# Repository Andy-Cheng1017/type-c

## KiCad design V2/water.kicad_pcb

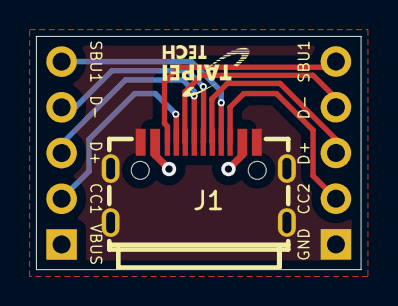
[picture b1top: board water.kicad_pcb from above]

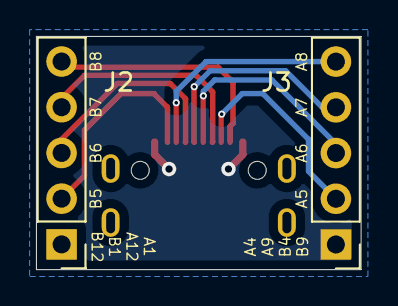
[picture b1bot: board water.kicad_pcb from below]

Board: 2 copper layers, 18.0 x 13.0 mm, 3 parts (2 on the bottom side), 10 nets.

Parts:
J1: USB_C_Receptacle_USB2.0; USB-C-SMD_TYPE-C-31-E-03
J2, J3: Conn_01x05; PinHeader_1x05_P2.54mm_Vertical

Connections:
unnamed: J1.A1 (GND), J1.A12 (GND), J1.B1 (GND), J1.B12 (GND), J1.S1 (SHIELD), J2.1
unnamed: J1.A4 (VBUS), J1.A9 (VBUS), J1.B4 (VBUS), J1.B9 (VBUS), J3.1
unnamed: J1.A5 (CC1), J3.2
unnamed: J1.A6 (D+), J3.3
unnamed: J1.A7 (D-), J3.4
unnamed: J1.A8 (SBU1), J3.5
unnamed: J1.B5 (CC2), J2.2
unnamed: J1.B6 (D+), J2.3
unnamed: J1.B7 (D-), J2.4
unnamed: J1.B8 (SBU2), J2.5

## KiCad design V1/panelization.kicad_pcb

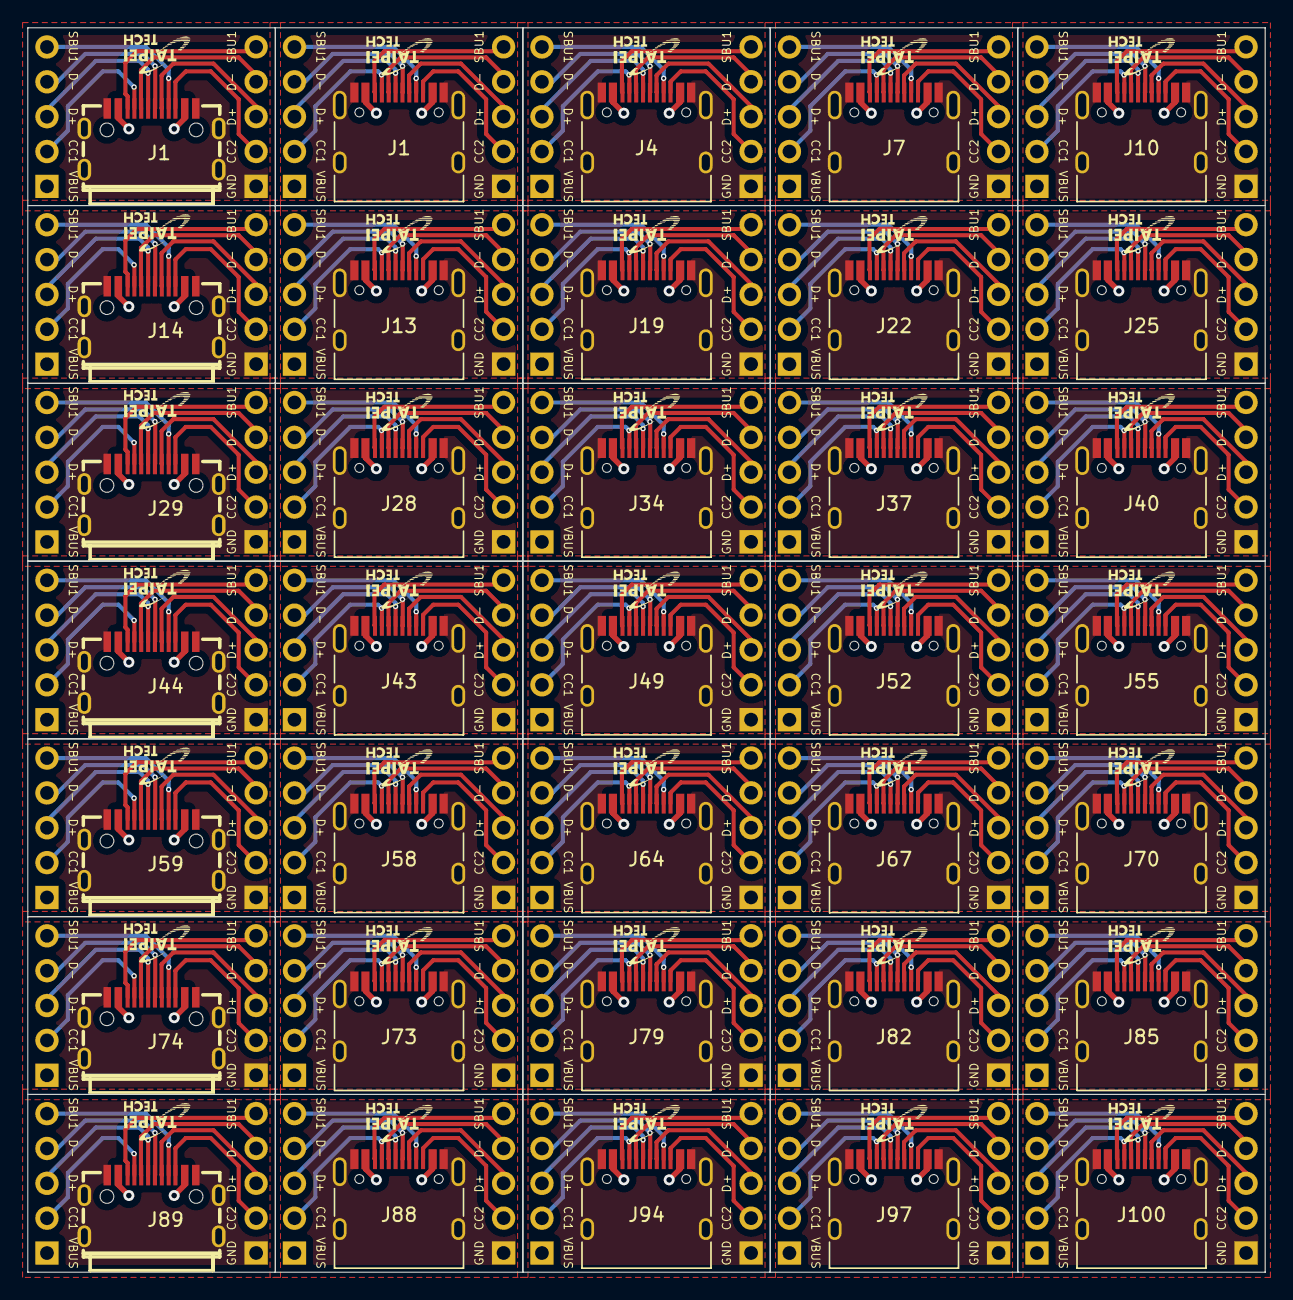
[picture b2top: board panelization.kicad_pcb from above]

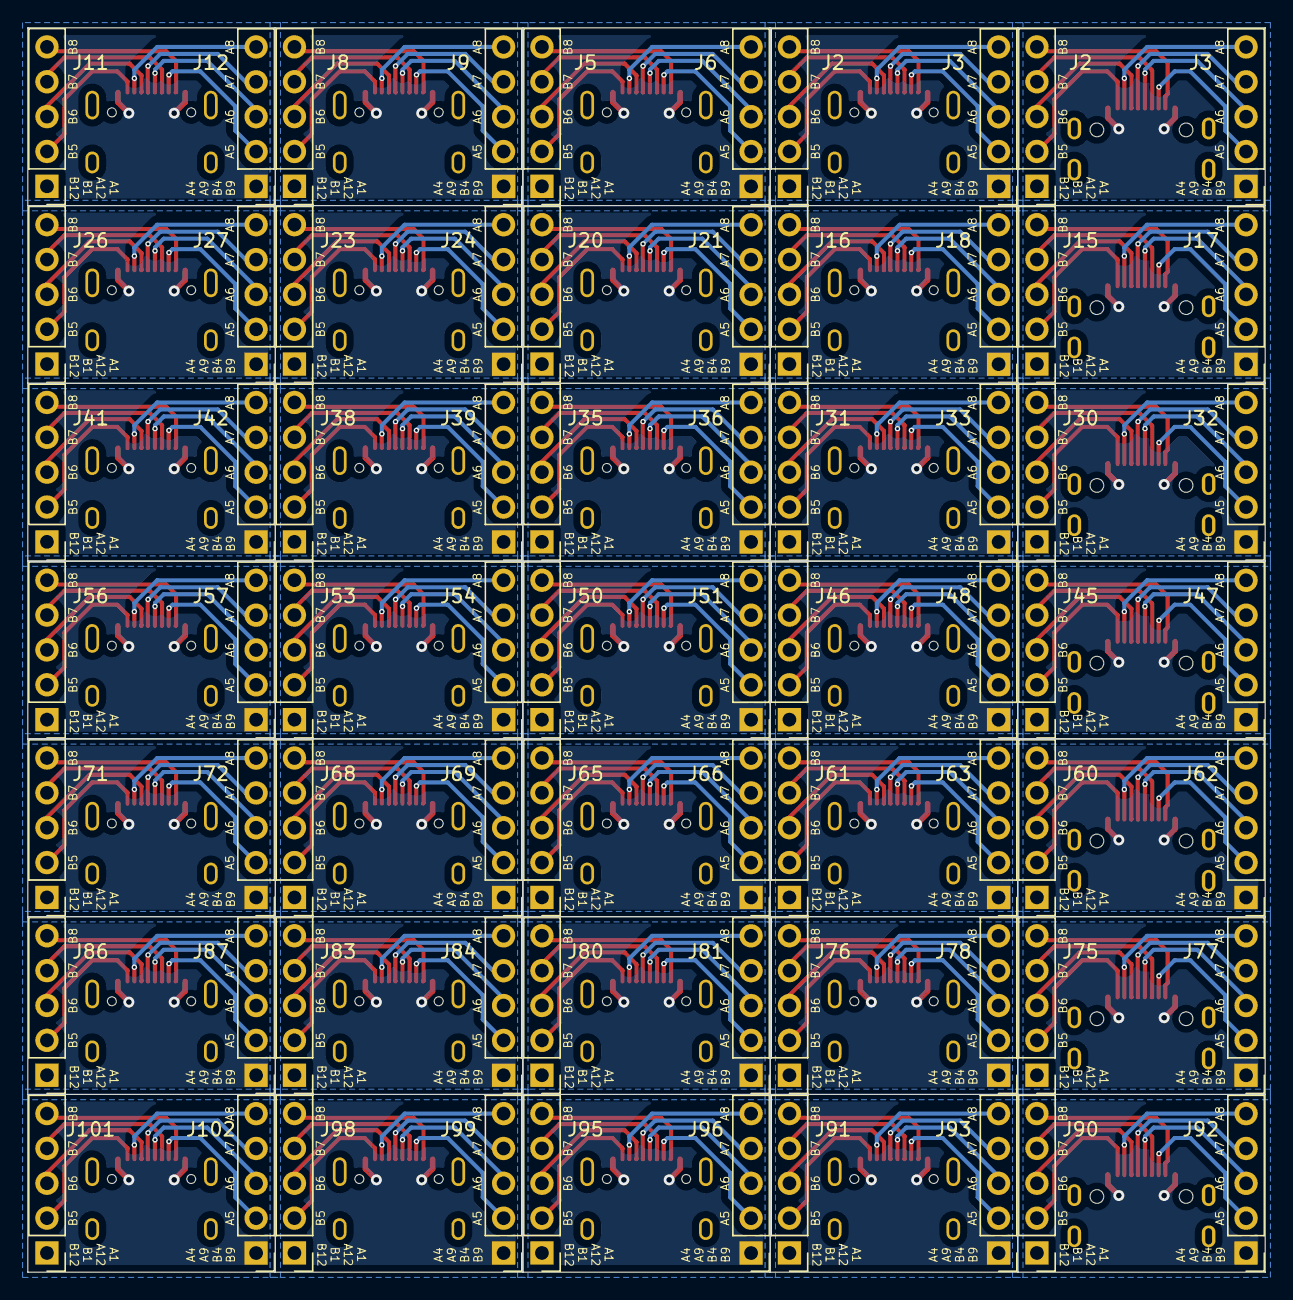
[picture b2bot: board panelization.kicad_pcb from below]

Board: 2 copper layers, 90.2 x 90.7 mm, 105 parts (70 on the bottom side), 10 nets.

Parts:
J1, J4, J7, J10, J13, J19, J22, J25, J28, J34, J37, J40, J43, J49, J52, J55, J58, J64, J67, J70, J73, J79, J82, J85, J88, J94, J97, J100: USB_C_Receptacle_USB2.0; USB_C_Receptacle_HRO_TYPE-C-31-M-12
J1#2, J14, J29, J44, J59, J74, J89: USB_C_Receptacle_USB2.0; USB-C-SMD_TYPE-C-31-E-03
J2, J2#2, J3, J3#2, J5, J6, J8, J9, J11, J12, J15, J16, J17, J18, J20, J21, J23, J24, J26, J27, J30, J31, J32, J33, J35, J36, J38, J39, J41, J42, J45, J46, J47, J48, J50, J51, J53, J54, J56, J57, J60, J61, J62, J63, J65, J66, J68, J69, J71, J72, J75, J76, J77, J78, J80, J81, J83, J84, J86, J87, J90, J91, J92, J93, J95, J96, J98, J99, J101, J102: Conn_01x05; PinHeader_1x05_P2.54mm_Vertical

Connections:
unnamed: J1.A1 (GND), J1.A12 (GND), J1.B1 (GND), J1.B12 (GND), J1.S1 (SHIELD), J1#2.A1 (GND), J1#2.A12 (GND), J1#2.B1 (GND), J1#2.B12 (GND), J1#2.S1 (SHIELD), J2.1, J2#2.1, J4.A1 (GND), J4.A12 (GND), J4.B1 (GND), J4.B12 (GND), J4.S1 (SHIELD), J5.1, J7.A1 (GND), J7.A12 (GND), J7.B1 (GND), J7.B12 (GND), J7.S1 (SHIELD), J8.1, J10.A1 (GND), J10.A12 (GND), J10.B1 (GND), J10.B12 (GND), J10.S1 (SHIELD), J11.1, J13.A1 (GND), J13.A12 (GND), J13.B1 (GND), J13.B12 (GND), J13.S1 (SHIELD), J14.A1 (GND), J14.A12 (GND), J14.B1 (GND), J14.B12 (GND), J14.S1 (SHIELD), J15.1, J16.1, J19.A1 (GND), J19.A12 (GND), J19.B1 (GND), J19.B12 (GND), J19.S1 (SHIELD), J20.1, J22.A1 (GND), J22.A12 (GND), J22.B1 (GND), J22.B12 (GND), J22.S1 (SHIELD), J23.1, J25.A1 (GND), J25.A12 (GND), J25.B1 (GND), J25.B12 (GND), J25.S1 (SHIELD), J26.1, J28.A1 (GND), J28.A12 (GND), J28.B1 (GND), J28.B12 (GND), J28.S1 (SHIELD), J29.A1 (GND), J29.A12 (GND), J29.B1 (GND), J29.B12 (GND), J29.S1 (SHIELD), J30.1, J31.1, J34.A1 (GND), J34.A12 (GND), J34.B1 (GND), J34.B12 (GND), J34.S1 (SHIELD), J35.1, J37.A1 (GND), J37.A12 (GND), J37.B1 (GND), J37.B12 (GND), J37.S1 (SHIELD), J38.1, J40.A1 (GND), J40.A12 (GND), J40.B1 (GND), J40.B12 (GND), J40.S1 (SHIELD), J41.1, J43.A1 (GND), J43.A12 (GND), J43.B1 (GND), J43.B12 (GND), J43.S1 (SHIELD), J44.A1 (GND), J44.A12 (GND), J44.B1 (GND), J44.B12 (GND), J44.S1 (SHIELD), J45.1, J46.1, J49.A1 (GND), J49.A12 (GND), J49.B1 (GND), J49.B12 (GND), J49.S1 (SHIELD), J50.1, J52.A1 (GND), J52.A12 (GND), J52.B1 (GND), J52.B12 (GND), J52.S1 (SHIELD), J53.1, J55.A1 (GND), J55.A12 (GND), J55.B1 (GND), J55.B12 (GND), J55.S1 (SHIELD), J56.1, J58.A1 (GND), J58.A12 (GND), J58.B1 (GND), J58.B12 (GND), J58.S1 (SHIELD), J59.A1 (GND), J59.A12 (GND), J59.B1 (GND), J59.B12 (GND), J59.S1 (SHIELD), J60.1, J61.1, J64.A1 (GND), J64.A12 (GND), J64.B1 (GND), J64.B12 (GND), J64.S1 (SHIELD), J65.1, J67.A1 (GND), J67.A12 (GND), J67.B1 (GND), J67.B12 (GND), J67.S1 (SHIELD), J68.1, J70.A1 (GND), J70.A12 (GND), J70.B1 (GND), J70.B12 (GND), J70.S1 (SHIELD), J71.1, J73.A1 (GND), J73.A12 (GND), J73.B1 (GND), J73.B12 (GND), J73.S1 (SHIELD), J74.A1 (GND), J74.A12 (GND), J74.B1 (GND), J74.B12 (GND), J74.S1 (SHIELD), J75.1, J76.1, J79.A1 (GND), J79.A12 (GND), J79.B1 (GND), J79.B12 (GND), J79.S1 (SHIELD), J80.1, J82.A1 (GND), J82.A12 (GND), J82.B1 (GND), J82.B12 (GND), J82.S1 (SHIELD), J83.1, J85.A1 (GND), J85.A12 (GND), J85.B1 (GND), J85.B12 (GND), J85.S1 (SHIELD), J86.1, J88.A1 (GND), J88.A12 (GND), J88.B1 (GND), J88.B12 (GND), J88.S1 (SHIELD), J89.A1 (GND), J89.A12 (GND), J89.B1 (GND), J89.B12 (GND), J89.S1 (SHIELD), J90.1, J91.1, J94.A1 (GND), J94.A12 (GND), J94.B1 (GND), J94.B12 (GND), J94.S1 (SHIELD), J95.1, J97.A1 (GND), J97.A12 (GND), J97.B1 (GND), J97.B12 (GND), J97.S1 (SHIELD), J98.1, J100.A1 (GND), J100.A12 (GND), J100.B1 (GND), J100.B12 (GND), J100.S1 (SHIELD), J101.1
unnamed: J1.A4 (VBUS), J1.A9 (VBUS), J1.B4 (VBUS), J1.B9 (VBUS), J1#2.A4 (VBUS), J1#2.A9 (VBUS), J1#2.B4 (VBUS), J1#2.B9 (VBUS), J3.1, J3#2.1, J4.A4 (VBUS), J4.A9 (VBUS), J4.B4 (VBUS), J4.B9 (VBUS), J6.1, J7.A4 (VBUS), J7.A9 (VBUS), J7.B4 (VBUS), J7.B9 (VBUS), J9.1, J10.A4 (VBUS), J10.A9 (VBUS), J10.B4 (VBUS), J10.B9 (VBUS), J12.1, J13.A4 (VBUS), J13.A9 (VBUS), J13.B4 (VBUS), J13.B9 (VBUS), J14.A4 (VBUS), J14.A9 (VBUS), J14.B4 (VBUS), J14.B9 (VBUS), J17.1, J18.1, J19.A4 (VBUS), J19.A9 (VBUS), J19.B4 (VBUS), J19.B9 (VBUS), J21.1, J22.A4 (VBUS), J22.A9 (VBUS), J22.B4 (VBUS), J22.B9 (VBUS), J24.1, J25.A4 (VBUS), J25.A9 (VBUS), J25.B4 (VBUS), J25.B9 (VBUS), J27.1, J28.A4 (VBUS), J28.A9 (VBUS), J28.B4 (VBUS), J28.B9 (VBUS), J29.A4 (VBUS), J29.A9 (VBUS), J29.B4 (VBUS), J29.B9 (VBUS), J32.1, J33.1, J34.A4 (VBUS), J34.A9 (VBUS), J34.B4 (VBUS), J34.B9 (VBUS), J36.1, J37.A4 (VBUS), J37.A9 (VBUS), J37.B4 (VBUS), J37.B9 (VBUS), J39.1, J40.A4 (VBUS), J40.A9 (VBUS), J40.B4 (VBUS), J40.B9 (VBUS), J42.1, J43.A4 (VBUS), J43.A9 (VBUS), J43.B4 (VBUS), J43.B9 (VBUS), J44.A4 (VBUS), J44.A9 (VBUS), J44.B4 (VBUS), J44.B9 (VBUS), J47.1, J48.1, J49.A4 (VBUS), J49.A9 (VBUS), J49.B4 (VBUS), J49.B9 (VBUS), J51.1, J52.A4 (VBUS), J52.A9 (VBUS), J52.B4 (VBUS), J52.B9 (VBUS), J54.1, J55.A4 (VBUS), J55.A9 (VBUS), J55.B4 (VBUS), J55.B9 (VBUS), J57.1, J58.A4 (VBUS), J58.A9 (VBUS), J58.B4 (VBUS), J58.B9 (VBUS), J59.A4 (VBUS), J59.A9 (VBUS), J59.B4 (VBUS), J59.B9 (VBUS), J62.1, J63.1, J64.A4 (VBUS), J64.A9 (VBUS), J64.B4 (VBUS), J64.B9 (VBUS), J66.1, J67.A4 (VBUS), J67.A9 (VBUS), J67.B4 (VBUS), J67.B9 (VBUS), J69.1, J70.A4 (VBUS), J70.A9 (VBUS), J70.B4 (VBUS), J70.B9 (VBUS), J72.1, J73.A4 (VBUS), J73.A9 (VBUS), J73.B4 (VBUS), J73.B9 (VBUS), J74.A4 (VBUS), J74.A9 (VBUS), J74.B4 (VBUS), J74.B9 (VBUS), J77.1, J78.1, J79.A4 (VBUS), J79.A9 (VBUS), J79.B4 (VBUS), J79.B9 (VBUS), J81.1, J82.A4 (VBUS), J82.A9 (VBUS), J82.B4 (VBUS), J82.B9 (VBUS), J84.1, J85.A4 (VBUS), J85.A9 (VBUS), J85.B4 (VBUS), J85.B9 (VBUS), J87.1, J88.A4 (VBUS), J88.A9 (VBUS), J88.B4 (VBUS), J88.B9 (VBUS), J89.A4 (VBUS), J89.A9 (VBUS), J89.B4 (VBUS), J89.B9 (VBUS), J92.1, J93.1, J94.A4 (VBUS), J94.A9 (VBUS), J94.B4 (VBUS), J94.B9 (VBUS), J96.1, J97.A4 (VBUS), J97.A9 (VBUS), J97.B4 (VBUS), J97.B9 (VBUS), J99.1, J100.A4 (VBUS), J100.A9 (VBUS), J100.B4 (VBUS), J100.B9 (VBUS), J102.1
unnamed: J1.A5 (CC1), J1#2.A5 (CC1), J3.2, J3#2.2, J4.A5 (CC1), J6.2, J7.A5 (CC1), J9.2, J10.A5 (CC1), J12.2, J13.A5 (CC1), J14.A5 (CC1), J17.2, J18.2, J19.A5 (CC1), J21.2, J22.A5 (CC1), J24.2, J25.A5 (CC1), J27.2, J28.A5 (CC1), J29.A5 (CC1), J32.2, J33.2, J34.A5 (CC1), J36.2, J37.A5 (CC1), J39.2, J40.A5 (CC1), J42.2, J43.A5 (CC1), J44.A5 (CC1), J47.2, J48.2, J49.A5 (CC1), J51.2, J52.A5 (CC1), J54.2, J55.A5 (CC1), J57.2, J58.A5 (CC1), J59.A5 (CC1), J62.2, J63.2, J64.A5 (CC1), J66.2, J67.A5 (CC1), J69.2, J70.A5 (CC1), J72.2, J73.A5 (CC1), J74.A5 (CC1), J77.2, J78.2, J79.A5 (CC1), J81.2, J82.A5 (CC1), J84.2, J85.A5 (CC1), J87.2, J88.A5 (CC1), J89.A5 (CC1), J92.2, J93.2, J94.A5 (CC1), J96.2, J97.A5 (CC1), J99.2, J100.A5 (CC1), J102.2
unnamed: J1.A6 (D+), J1#2.A6 (D+), J3.3, J3#2.3, J4.A6 (D+), J6.3, J7.A6 (D+), J9.3, J10.A6 (D+), J12.3, J13.A6 (D+), J14.A6 (D+), J17.3, J18.3, J19.A6 (D+), J21.3, J22.A6 (D+), J24.3, J25.A6 (D+), J27.3, J28.A6 (D+), J29.A6 (D+), J32.3, J33.3, J34.A6 (D+), J36.3, J37.A6 (D+), J39.3, J40.A6 (D+), J42.3, J43.A6 (D+), J44.A6 (D+), J47.3, J48.3, J49.A6 (D+), J51.3, J52.A6 (D+), J54.3, J55.A6 (D+), J57.3, J58.A6 (D+), J59.A6 (D+), J62.3, J63.3, J64.A6 (D+), J66.3, J67.A6 (D+), J69.3, J70.A6 (D+), J72.3, J73.A6 (D+), J74.A6 (D+), J77.3, J78.3, J79.A6 (D+), J81.3, J82.A6 (D+), J84.3, J85.A6 (D+), J87.3, J88.A6 (D+), J89.A6 (D+), J92.3, J93.3, J94.A6 (D+), J96.3, J97.A6 (D+), J99.3, J100.A6 (D+), J102.3
unnamed: J1.A7 (D-), J1#2.A7 (D-), J3.4, J3#2.4, J4.A7 (D-), J6.4, J7.A7 (D-), J9.4, J10.A7 (D-), J12.4, J13.A7 (D-), J14.A7 (D-), J17.4, J18.4, J19.A7 (D-), J21.4, J22.A7 (D-), J24.4, J25.A7 (D-), J27.4, J28.A7 (D-), J29.A7 (D-), J32.4, J33.4, J34.A7 (D-), J36.4, J37.A7 (D-), J39.4, J40.A7 (D-), J42.4, J43.A7 (D-), J44.A7 (D-), J47.4, J48.4, J49.A7 (D-), J51.4, J52.A7 (D-), J54.4, J55.A7 (D-), J57.4, J58.A7 (D-), J59.A7 (D-), J62.4, J63.4, J64.A7 (D-), J66.4, J67.A7 (D-), J69.4, J70.A7 (D-), J72.4, J73.A7 (D-), J74.A7 (D-), J77.4, J78.4, J79.A7 (D-), J81.4, J82.A7 (D-), J84.4, J85.A7 (D-), J87.4, J88.A7 (D-), J89.A7 (D-), J92.4, J93.4, J94.A7 (D-), J96.4, J97.A7 (D-), J99.4, J100.A7 (D-), J102.4
unnamed: J1.A8 (SBU1), J1#2.A8 (SBU1), J3.5, J3#2.5, J4.A8 (SBU1), J6.5, J7.A8 (SBU1), J9.5, J10.A8 (SBU1), J12.5, J13.A8 (SBU1), J14.A8 (SBU1), J17.5, J18.5, J19.A8 (SBU1), J21.5, J22.A8 (SBU1), J24.5, J25.A8 (SBU1), J27.5, J28.A8 (SBU1), J29.A8 (SBU1), J32.5, J33.5, J34.A8 (SBU1), J36.5, J37.A8 (SBU1), J39.5, J40.A8 (SBU1), J42.5, J43.A8 (SBU1), J44.A8 (SBU1), J47.5, J48.5, J49.A8 (SBU1), J51.5, J52.A8 (SBU1), J54.5, J55.A8 (SBU1), J57.5, J58.A8 (SBU1), J59.A8 (SBU1), J62.5, J63.5, J64.A8 (SBU1), J66.5, J67.A8 (SBU1), J69.5, J70.A8 (SBU1), J72.5, J73.A8 (SBU1), J74.A8 (SBU1), J77.5, J78.5, J79.A8 (SBU1), J81.5, J82.A8 (SBU1), J84.5, J85.A8 (SBU1), J87.5, J88.A8 (SBU1), J89.A8 (SBU1), J92.5, J93.5, J94.A8 (SBU1), J96.5, J97.A8 (SBU1), J99.5, J100.A8 (SBU1), J102.5
unnamed: J1.B5 (CC2), J1#2.B5 (CC2), J2.2, J2#2.2, J4.B5 (CC2), J5.2, J7.B5 (CC2), J8.2, J10.B5 (CC2), J11.2, J13.B5 (CC2), J14.B5 (CC2), J15.2, J16.2, J19.B5 (CC2), J20.2, J22.B5 (CC2), J23.2, J25.B5 (CC2), J26.2, J28.B5 (CC2), J29.B5 (CC2), J30.2, J31.2, J34.B5 (CC2), J35.2, J37.B5 (CC2), J38.2, J40.B5 (CC2), J41.2, J43.B5 (CC2), J44.B5 (CC2), J45.2, J46.2, J49.B5 (CC2), J50.2, J52.B5 (CC2), J53.2, J55.B5 (CC2), J56.2, J58.B5 (CC2), J59.B5 (CC2), J60.2, J61.2, J64.B5 (CC2), J65.2, J67.B5 (CC2), J68.2, J70.B5 (CC2), J71.2, J73.B5 (CC2), J74.B5 (CC2), J75.2, J76.2, J79.B5 (CC2), J80.2, J82.B5 (CC2), J83.2, J85.B5 (CC2), J86.2, J88.B5 (CC2), J89.B5 (CC2), J90.2, J91.2, J94.B5 (CC2), J95.2, J97.B5 (CC2), J98.2, J100.B5 (CC2), J101.2
unnamed: J1.B6 (D+), J1#2.B6 (D+), J2.3, J2#2.3, J4.B6 (D+), J5.3, J7.B6 (D+), J8.3, J10.B6 (D+), J11.3, J13.B6 (D+), J14.B6 (D+), J15.3, J16.3, J19.B6 (D+), J20.3, J22.B6 (D+), J23.3, J25.B6 (D+), J26.3, J28.B6 (D+), J29.B6 (D+), J30.3, J31.3, J34.B6 (D+), J35.3, J37.B6 (D+), J38.3, J40.B6 (D+), J41.3, J43.B6 (D+), J44.B6 (D+), J45.3, J46.3, J49.B6 (D+), J50.3, J52.B6 (D+), J53.3, J55.B6 (D+), J56.3, J58.B6 (D+), J59.B6 (D+), J60.3, J61.3, J64.B6 (D+), J65.3, J67.B6 (D+), J68.3, J70.B6 (D+), J71.3, J73.B6 (D+), J74.B6 (D+), J75.3, J76.3, J79.B6 (D+), J80.3, J82.B6 (D+), J83.3, J85.B6 (D+), J86.3, J88.B6 (D+), J89.B6 (D+), J90.3, J91.3, J94.B6 (D+), J95.3, J97.B6 (D+), J98.3, J100.B6 (D+), J101.3
unnamed: J1.B7 (D-), J1#2.B7 (D-), J2.4, J2#2.4, J4.B7 (D-), J5.4, J7.B7 (D-), J8.4, J10.B7 (D-), J11.4, J13.B7 (D-), J14.B7 (D-), J15.4, J16.4, J19.B7 (D-), J20.4, J22.B7 (D-), J23.4, J25.B7 (D-), J26.4, J28.B7 (D-), J29.B7 (D-), J30.4, J31.4, J34.B7 (D-), J35.4, J37.B7 (D-), J38.4, J40.B7 (D-), J41.4, J43.B7 (D-), J44.B7 (D-), J45.4, J46.4, J49.B7 (D-), J50.4, J52.B7 (D-), J53.4, J55.B7 (D-), J56.4, J58.B7 (D-), J59.B7 (D-), J60.4, J61.4, J64.B7 (D-), J65.4, J67.B7 (D-), J68.4, J70.B7 (D-), J71.4, J73.B7 (D-), J74.B7 (D-), J75.4, J76.4, J79.B7 (D-), J80.4, J82.B7 (D-), J83.4, J85.B7 (D-), J86.4, J88.B7 (D-), J89.B7 (D-), J90.4, J91.4, J94.B7 (D-), J95.4, J97.B7 (D-), J98.4, J100.B7 (D-), J101.4
unnamed: J1.B8 (SBU2), J1#2.B8 (SBU2), J2.5, J2#2.5, J4.B8 (SBU2), J5.5, J7.B8 (SBU2), J8.5, J10.B8 (SBU2), J11.5, J13.B8 (SBU2), J14.B8 (SBU2), J15.5, J16.5, J19.B8 (SBU2), J20.5, J22.B8 (SBU2), J23.5, J25.B8 (SBU2), J26.5, J28.B8 (SBU2), J29.B8 (SBU2), J30.5, J31.5, J34.B8 (SBU2), J35.5, J37.B8 (SBU2), J38.5, J40.B8 (SBU2), J41.5, J43.B8 (SBU2), J44.B8 (SBU2), J45.5, J46.5, J49.B8 (SBU2), J50.5, J52.B8 (SBU2), J53.5, J55.B8 (SBU2), J56.5, J58.B8 (SBU2), J59.B8 (SBU2), J60.5, J61.5, J64.B8 (SBU2), J65.5, J67.B8 (SBU2), J68.5, J70.B8 (SBU2), J71.5, J73.B8 (SBU2), J74.B8 (SBU2), J75.5, J76.5, J79.B8 (SBU2), J80.5, J82.B8 (SBU2), J83.5, J85.B8 (SBU2), J86.5, J88.B8 (SBU2), J89.B8 (SBU2), J90.5, J91.5, J94.B8 (SBU2), J95.5, J97.B8 (SBU2), J98.5, J100.B8 (SBU2), J101.5
